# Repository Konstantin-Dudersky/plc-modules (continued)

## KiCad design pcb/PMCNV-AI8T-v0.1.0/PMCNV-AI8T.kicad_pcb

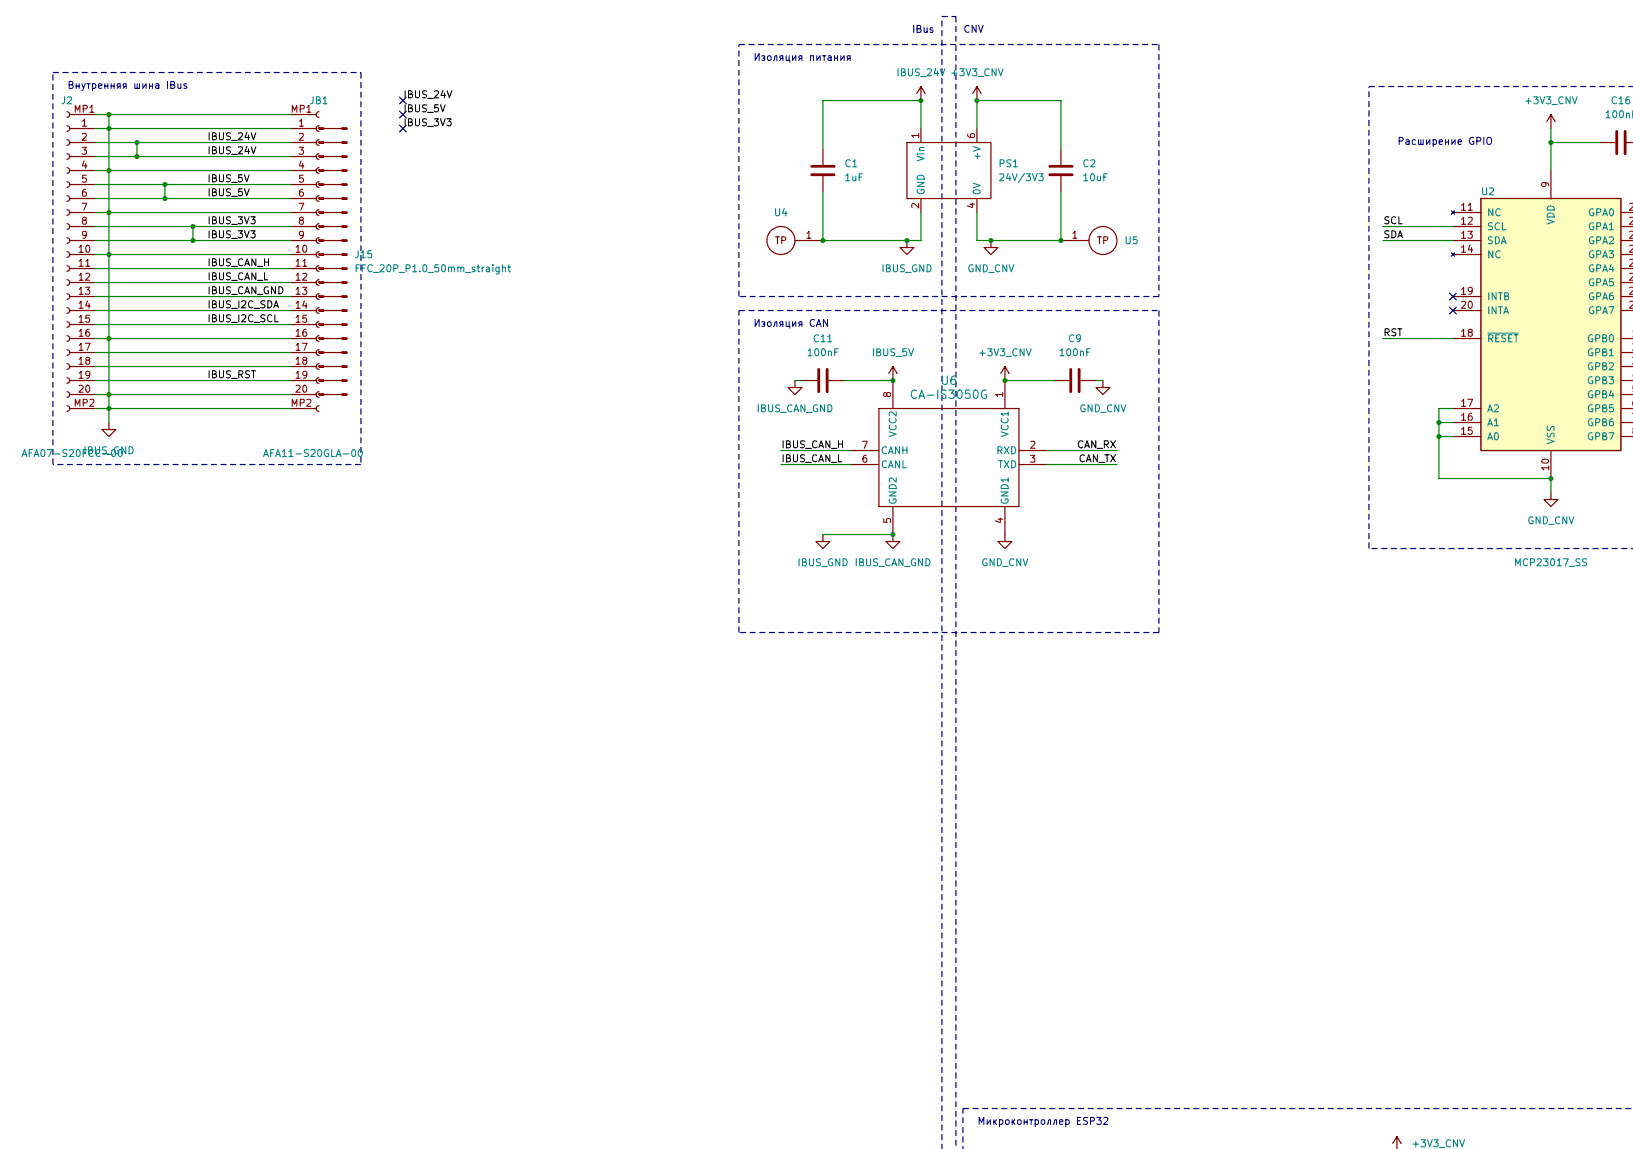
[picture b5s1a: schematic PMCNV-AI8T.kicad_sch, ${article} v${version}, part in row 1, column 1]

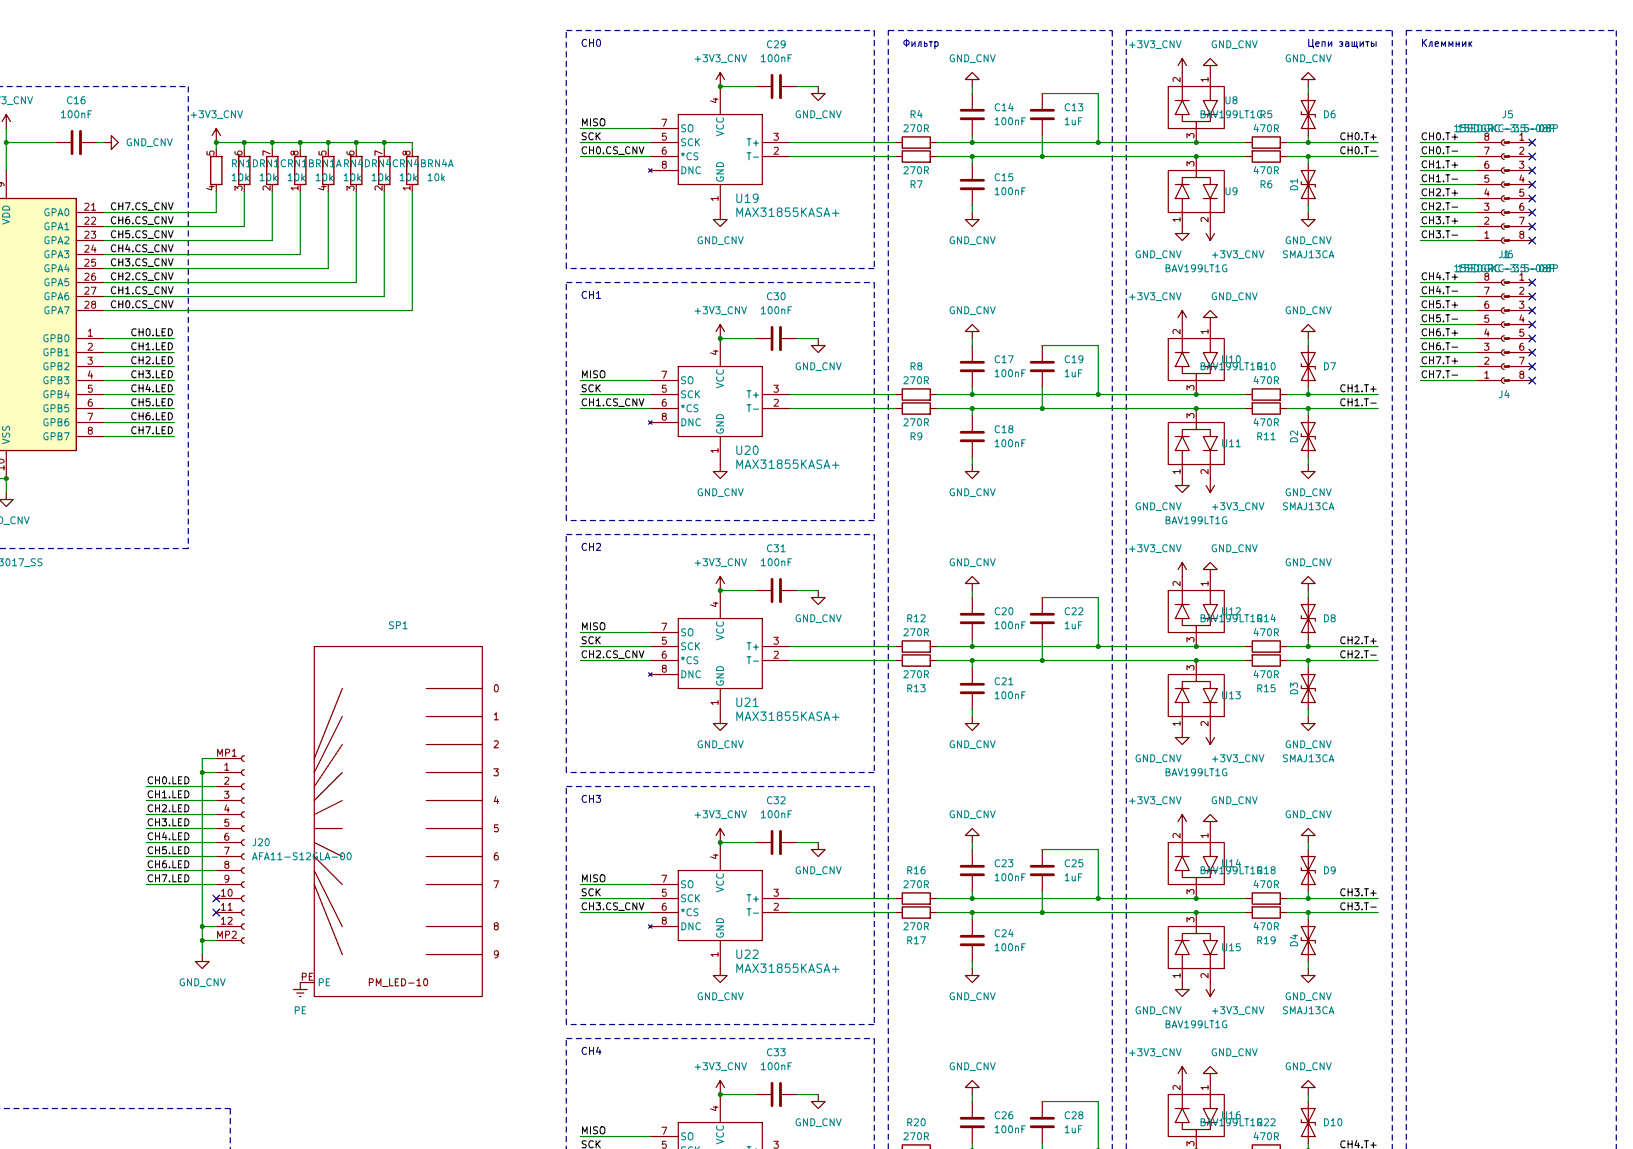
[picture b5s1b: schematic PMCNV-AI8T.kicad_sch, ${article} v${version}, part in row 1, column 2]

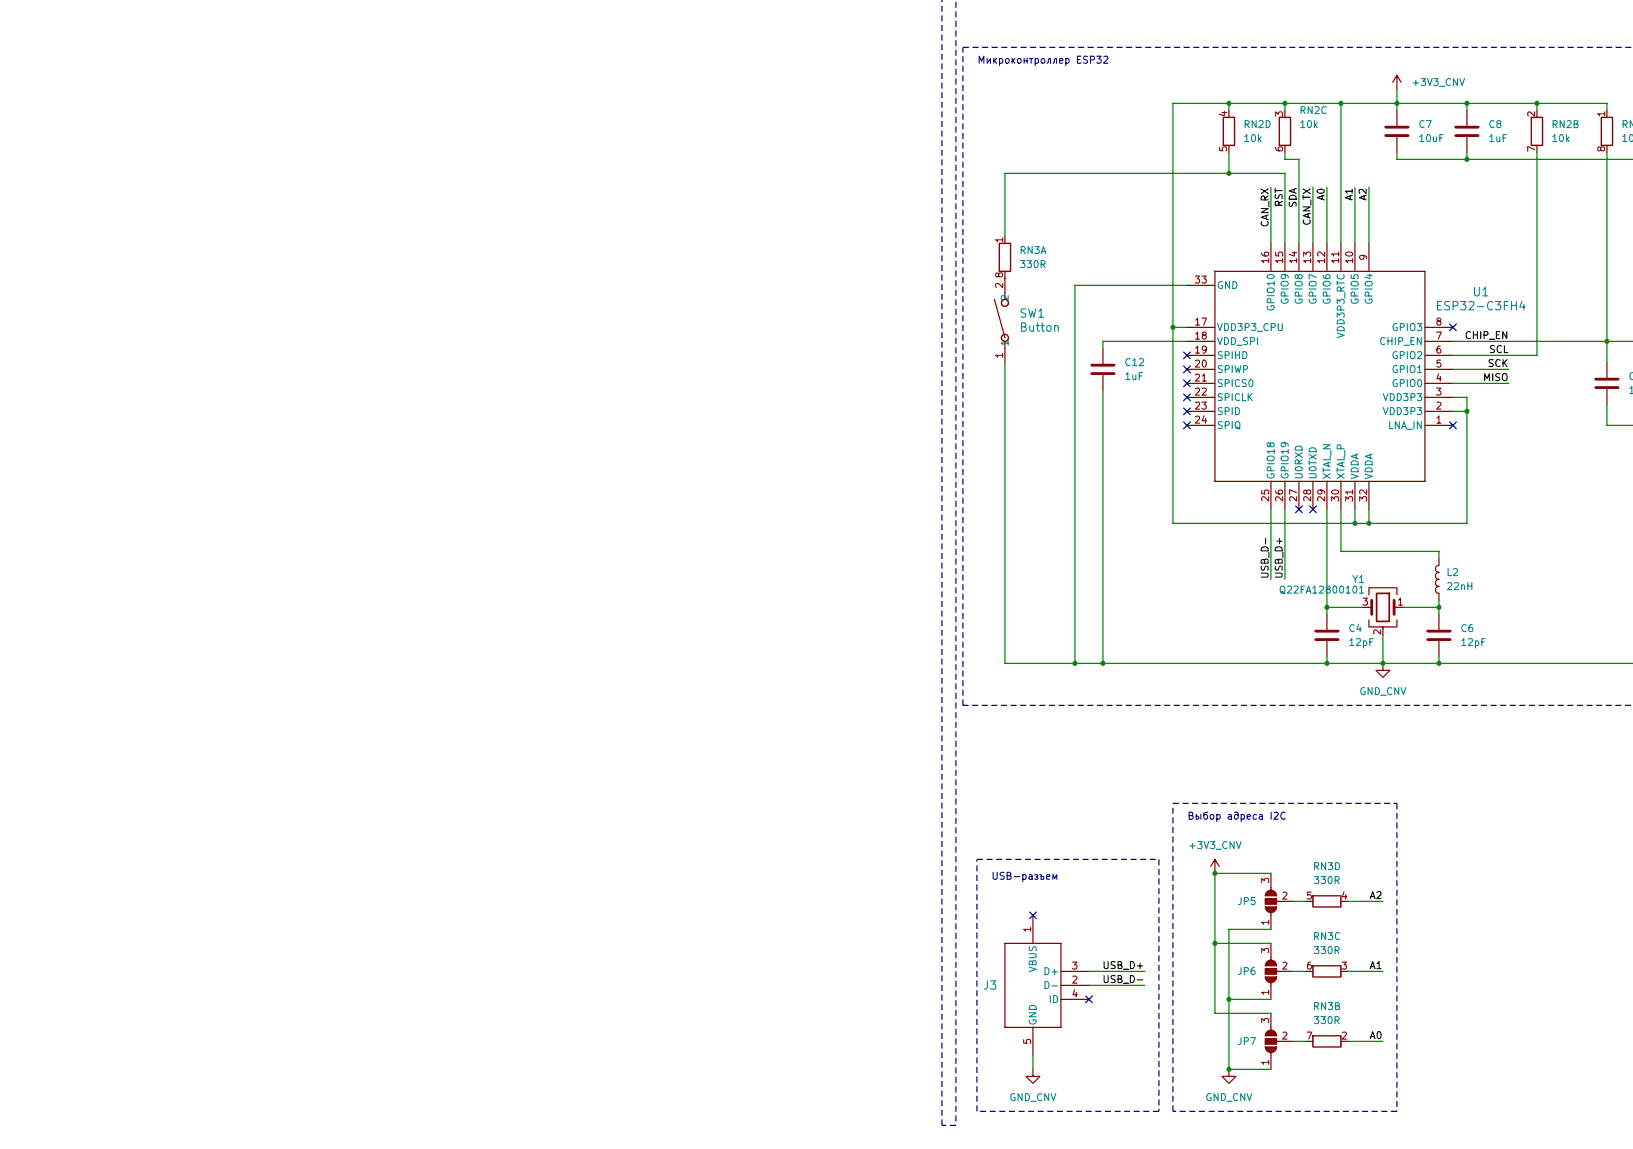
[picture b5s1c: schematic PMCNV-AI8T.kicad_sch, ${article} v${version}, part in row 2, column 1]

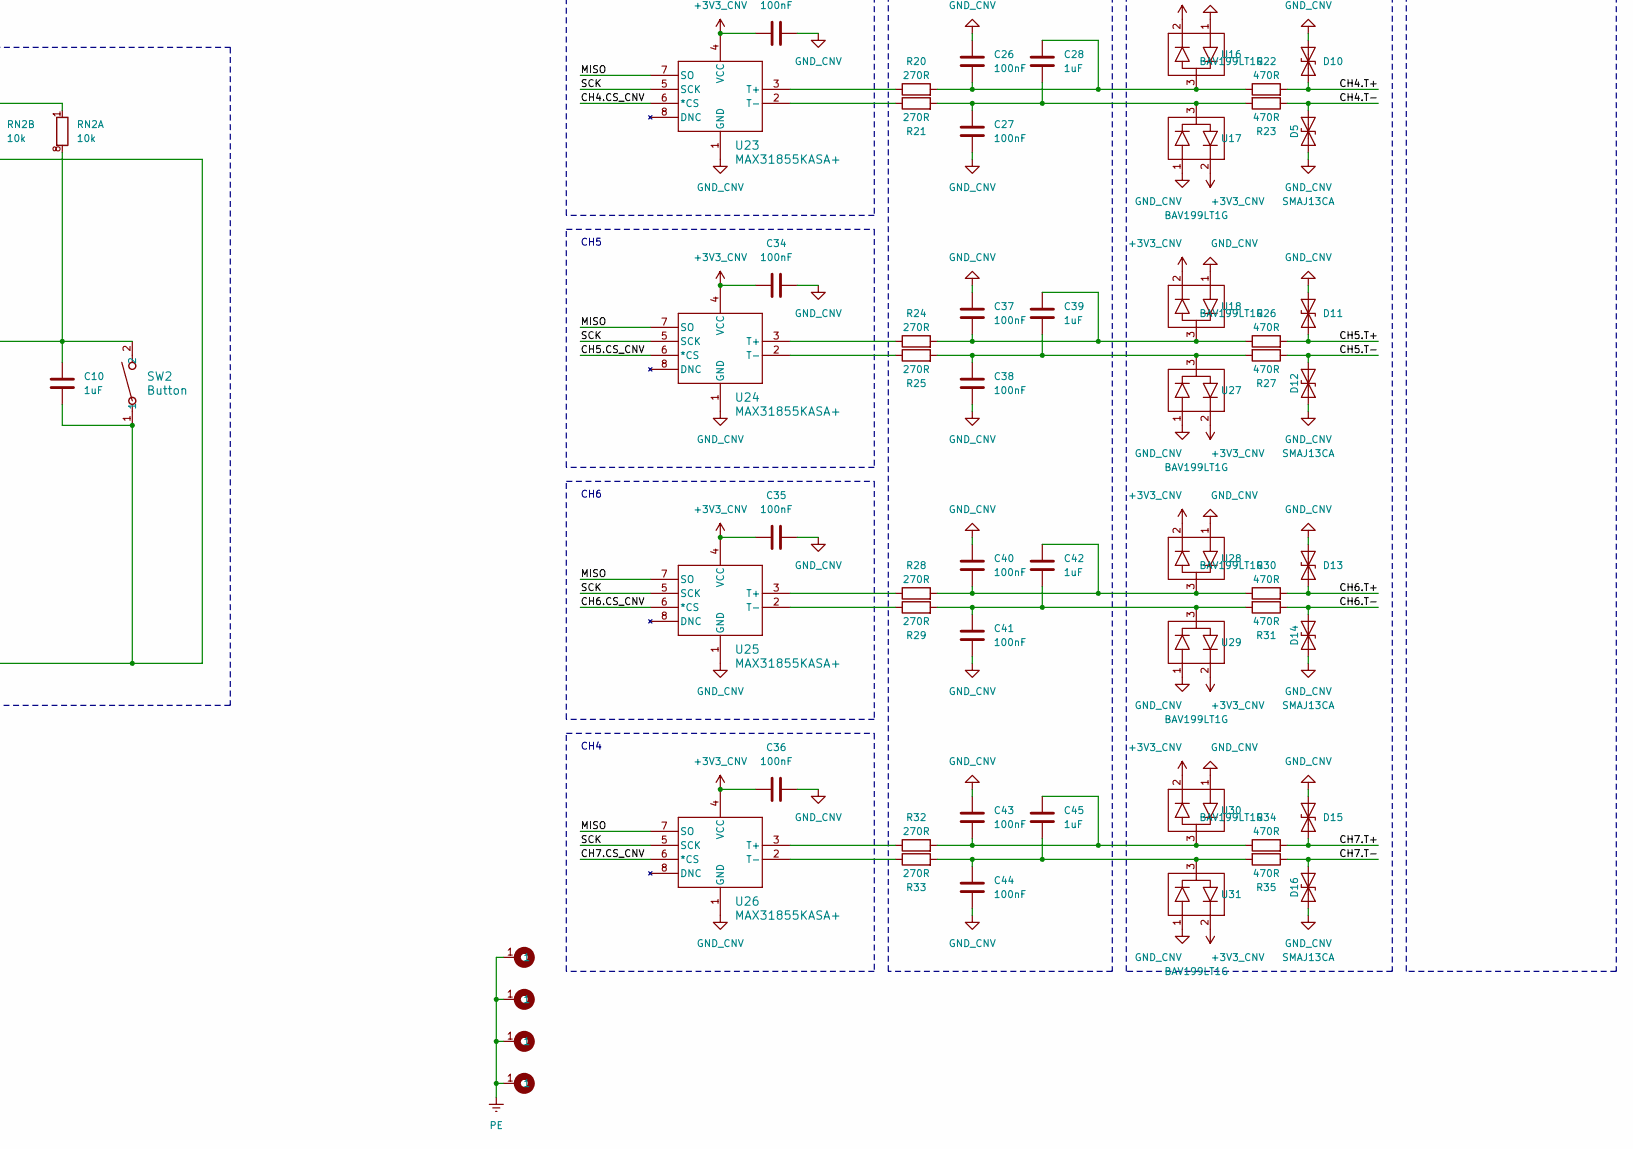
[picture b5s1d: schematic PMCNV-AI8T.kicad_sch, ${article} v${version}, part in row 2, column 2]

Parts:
C1, C8, C10, C12, C13, C19, C22, C25, C28, C39, C42, C45: 1uF; C_0603_1608Metric; part_ipn C_1uF_50V_0603_MLCC-X7R
C2, C7: 10uF; C_1206_3216Metric; part_ipn C_10uF_50V_1206_MLCC-X7R
C4, C6: 12pF; C_0603_1608Metric; part_ipn C_12pF_100V_0603_MLCC-NP0
C9, C11, C14, C15, C16, C17, C18, C20, C21, C23, C24, C26, C27, C29, C30, C31, C32, C33, C34, C35, C36, C37, C38, C40, C41, C43, C44: 100nF; C_0603_1608Metric; part_ipn C_100nF_100V_0603_MLCC-X7R
D1, D2, D3, D4, D5, D6, D7, D8, D9, D10, D11, D12, D13, D14, D15, D16: SMAJ13CA; SMASeries_LTF; part_ipn SMAJ13CA
H4, H5, H6, H7: M4; MountingHole_4.3mm_M4_Pad_Via
J1, J4: 15EDGRC-3.5-08P; part_ipn 15EDGRC-3.5-08P
J2: AFA07-S20FCC-00; AFA07S20FCA00; part_ipn AFA07-S20FCC-00
J3: U254-051T-4BH83-S1S; CONN5_H83-S1S_XKB; part_ipn U254-051T-4BH83-S1S
J5, J6: 15EDGKC-3.5-08P; part_ipn 15EDGKC-3.5-08P
J15: FFC_20P_P1.0_50mm_straight; part_ipn FFC_20P_P1.0_50mm_straight
J20: AFA11-S12GLA-00; part_ipn AFA11-S12GLA-00
JB1: AFA11-S20GLA-00; part_ipn AFA11-S20GLA-00
JP5, JP6, JP7: SolderJumper_3_Open; SolderJumper-3_P1.3mm_Open_Pad1.0x1.5mm
L2: 22nH; L_0603_1608Metric; part_ipn L_22nH_0603
PS1: 24V/3V3; B2405LS-1WR3; part_ipn B2403LS-1W
R4, R7, R8, R9, R12, R13, R16, R17, R20, R21, R24, R25, R28, R29, R32, R33: 270R; R_0603_1608Metric; part_ipn R_270R_0603_1%
R5, R6, R10, R11, R14, R15, R18, R19, R22, R23, R26, R27, R30, R31, R34, R35: 470R; R_0603_1608Metric; part_ipn R_470R_0603_1%
RN1, RN2, RN4: 10k; R_Array_Convex_4x0603; part_ipn R_10k_0603x4_1%
RN3: 330R; R_Array_Convex_4x0603; part_ipn R_330R_0603x4_1%
SP1: PMLED-xx-v0.0.3; part_ipn PMLED-10-v0.0.2
SW1, SW2: Button; SW_TS-1088_XNP-M; part_ipn TS-1088-AR02016
U1: ESP32-C3FH4; QFN32_5X5_EXP; part_ipn ESP32-C3FH4
U2: MCP23017_SS; SSOP28_MC_MCH; part_ipn MCP23017-E/SS
U4, U5: 5117; part_ipn Keystone_5117
U6: CA-IS3050G; SOIC8_CA-IS305_CLG; part_ipn CA-IS3050G
U8, U9, U10, U11, U12, U13, U14, U15, U16, U17, U18, U27, U28, U29, U30, U31: BAV199LT1G; SOT-23_ONS; part_ipn BAV199LT1G
U19, U20, U21, U22, U23, U24, U25, U26: MAX31855KASA+; 21-0041B_8_MXM; part_ipn MAX31855KASA+
Y1: Q22FA12800101; Crystal_SMD_2016-4Pin_2.0x1.6mm; part_ipn Q22FA12800101

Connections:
+3V3_CNV: C2.1, C7.1, C8.1, C9.1, C16.1, C29.1, C30.1, C31.1, C32.1, C33.1, C34.1, C35.1, C36.1, JP5.3 (B), JP6.3 (B), JP7.3 (B), PS1.6 (+V), RN1.5 (R4.2), RN1.6 (R3.2), RN1.7 (R2.2), RN1.8 (R1.2), RN2.1 (R1.1), RN2.2 (R2.1), RN2.3 (R3.1), RN2.4 (R4.1), RN4.5 (R4.2), RN4.6 (R3.2), RN4.7 (R2.2), RN4.8 (R1.2), U1.2 (VDD3P3), U1.3 (VDD3P3), U1.11 (VDD3P3_RTC), U1.17 (VDD3P3_CPU), U1.31 (VDDA), U1.32 (VDDA), U2.9 (VDD), U6.1 (VCC1), U8.2, U9.2, U10.2, U11.2, U12.2, U13.2, U14.2, U15.2, U16.2, U17.2, U18.2, U19.4 (VCC), U20.4 (VCC), U21.4 (VCC), U22.4 (VCC), U23.4 (VCC), U24.4 (VCC), U25.4 (VCC), U26.4 (VCC), U27.2, U28.2, U29.2, U30.2, U31.2
/A0: RN3.2 (R2.1), U1.12 (GPIO6)
/A1: RN3.3 (R3.1), U1.10 (GPIO5)
/A2: RN3.4 (R4.1), U1.9 (GPIO4)
/CAN_RX: U1.16 (GPIO10), U6.2 (RXD)
/CAN_TX: U1.13 (GPIO7), U6.3 (TXD)
/CH0.CS_CNV: RN4.1 (R1.1), U2.28 (GPA7), U19.6 (*CS)
/CH0.LED: J20.2, U2.1 (GPB0)
/CH0.T+: D6.2 (A2), J1.8, R5.2
/CH0.T-: D1.2 (A2), J1.7, R6.1
/CH1.CS_CNV: RN4.2 (R2.1), U2.27 (GPA6), U20.6 (*CS)
/CH1.LED: J20.3, U2.2 (GPB1)
/CH1.T+: D7.2 (A2), J1.6, R10.2
/CH1.T-: D2.2 (A2), J1.5, R11.1
/CH2.CS_CNV: RN4.3 (R3.1), U2.26 (GPA5), U21.6 (*CS)
/CH2.LED: J20.4, U2.3 (GPB2)
/CH2.T+: D8.2 (A2), J1.4, R14.2
/CH2.T-: D3.2 (A2), J1.3, R15.1
/CH3.CS_CNV: RN4.4 (R4.1), U2.25 (GPA4), U22.6 (*CS)
/CH3.LED: J20.5, U2.4 (GPB3)
/CH3.T+: D9.2 (A2), J1.2, R18.2
/CH3.T-: D4.2 (A2), J1.1, R19.1
/CH4.CS_CNV: RN1.1 (R1.1), U2.24 (GPA3), U23.6 (*CS)
/CH4.LED: J20.6, U2.5 (GPB4)
/CH4.T+: D10.2 (A2), J4.8, R22.2
/CH4.T-: D5.2 (A2), J4.7, R23.1
/CH5.CS_CNV: RN1.2 (R2.1), U2.23 (GPA2), U24.6 (*CS)
/CH5.LED: J20.7, U2.6 (GPB5)
/CH5.T+: D11.2 (A2), J4.6, R26.2
/CH5.T-: D12.2 (A2), J4.5, R27.1
/CH6.CS_CNV: RN1.3 (R3.1), U2.22 (GPA1), U25.6 (*CS)
/CH6.LED: J20.8, U2.7 (GPB6)
/CH6.T+: D13.2 (A2), J4.4, R30.2
/CH6.T-: D14.2 (A2), J4.3, R31.1
/CH7.CS_CNV: RN1.4 (R4.1), U2.21 (GPA0), U26.6 (*CS)
/CH7.LED: J20.9, U2.8 (GPB7)
/CH7.T+: D15.2 (A2), J4.2, R34.2
/CH7.T-: D16.2 (A2), J4.1, R35.1
/CHIP_EN: C10.1, RN2.8 (R1.2), SW2.2, U1.7 (CHIP_EN)
/IBUS_3V3: J2.8, J2.9, JB1.8, JB1.9
/IBUS_CAN_H: J2.11, JB1.11, U6.7 (CANH)
/IBUS_CAN_L: J2.12 (Pin_11), JB1.12 (Pin_11), U6.6 (CANL)
/IBUS_I2C_SCL: J2.15 (Pin_11), JB1.15 (Pin_11)
/IBUS_I2C_SDA: J2.14 (Pin_11), JB1.14 (Pin_11)
/IBUS_RST: J2.19 (Pin_11), JB1.19 (Pin_11)
/MISO: U1.4 (GPIO0), U19.7 (SO), U20.7 (SO), U21.7 (SO), U22.7 (SO), U23.7 (SO), U24.7 (SO), U25.7 (SO), U26.7 (SO)
/RST: RN2.5 (R4.2), RN3.1 (R1.1), U1.15 (GPIO9), U2.18 (~RESET)
/SCK: U1.5 (GPIO1), U19.5 (SCK), U20.5 (SCK), U21.5 (SCK), U22.5 (SCK), U23.5 (SCK), U24.5 (SCK), U25.5 (SCK), U26.5 (SCK)
/SCL: RN2.7 (R2.2), U1.6 (GPIO2), U2.12 (SCL)
/SDA: RN2.6 (R3.2), U1.14 (GPIO8), U2.13 (SDA)
/USB_D+: J3.3 (D+), U1.26 (GPIO19)
/USB_D-: J3.2 (D-), U1.25 (GPIO18)
GND_CNV: C2.2, C4.2, C6.2, C7.2, C8.2, C9.2, C10.2, C12.2, C14.1, C15.2, C16.2, C17.1, C18.2, C20.1, C21.2, C23.1, C24.2, C26.1, C27.2, C29.2, C30.2, C31.2, C32.2, C33.2, C34.2, C35.2, C36.2, C37.1, C38.2, C40.1, C41.2, C43.1, C44.2, D1.1 (A1), D2.1 (A1), D3.1 (A1), D4.1 (A1), D5.1 (A1), D6.1 (A1), D7.1 (A1), D8.1 (A1), D9.1 (A1), D10.1 (A1), D11.1 (A1), D12.1 (A1), D13.1 (A1), D14.1 (A1), D15.1 (A1), D16.1 (A1), J3.5 (GND), J20.1, J20.12 (Pin_11), J20.MP1 (Pin_11), J20.MP2 (Pin_11), JP5.1 (A), JP6.1 (A), JP7.1 (A), PS1.4 (0V), SW1.1, SW2.1, U1.33 (GND), U2.10 (VSS), U2.15 (A0), U2.16 (A1), U2.17 (A2), U5.1, U6.4 (GND1), U8.1, U9.1, U10.1, U11.1, U12.1, U13.1, U14.1, U15.1, U16.1, U17.1, U18.1, U19.1 (GND), U20.1 (GND), U21.1 (GND), U22.1 (GND), U23.1 (GND), U24.1 (GND), U25.1 (GND), U26.1 (GND), U27.1, U28.1, U29.1, U30.1, U31.1, Y1.2 (G), Y1.4 (G)
IBUS_5V: C11.2, J2.5, J2.6, JB1.5, JB1.6, U6.8 (VCC2)
IBUS_24V: C1.1, J2.2, J2.3, JB1.2, JB1.3, PS1.1 (Vin)
IBUS_CAN_GND: C1.2, C11.1, J2.1, J2.4, J2.7, J2.10, J2.13 (Pin_11), J2.16 (Pin_11), J2.20 (Pin_11), J2.MP1 (Pin_11), J2.MP2 (Pin_11), JB1.1, JB1.4, JB1.7, JB1.10, JB1.13 (Pin_11), JB1.16 (Pin_11), JB1.20 (Pin_11), JB1.MP1 (Pin_11), JB1.MP2 (Pin_11), PS1.2 (GND), U4.1, U6.5 (GND2)
unnamed: C6.1, L2.1, Y1.1
unnamed: C13.1, C14.2, R4.2, R5.1, U8.3
unnamed: C13.2, C15.1, R6.2, R7.2, U9.3
unnamed: C17.2, C19.1, R8.2, R10.1, U10.3
unnamed: C18.1, C19.2, R9.2, R11.2, U11.3
unnamed: C20.2, C22.1, R12.2, R14.1, U12.3
unnamed: C21.1, C22.2, R13.2, R15.2, U13.3
unnamed: C23.2, C25.1, R16.2, R18.1, U14.3
unnamed: C24.1, C25.2, R17.2, R19.2, U15.3
unnamed: C26.2, C28.1, R20.2, R22.1, U16.3
unnamed: C27.1, C28.2, R21.2, R23.2, U17.3
unnamed: C37.2, C39.1, R24.2, R26.1, U18.3
unnamed: C38.1, C39.2, R25.2, R27.2, U27.3
unnamed: C40.2, C42.1, R28.2, R30.1, U28.3
unnamed: C41.1, C42.2, R29.2, R31.2, U29.3
unnamed: C43.2, C45.1, R32.2, R34.1, U30.3
unnamed: C44.1, C45.2, R33.2, R35.2, U31.3
unnamed: J2.17 (Pin_11), JB1.17 (Pin_11)
unnamed: J2.18 (Pin_11), JB1.18 (Pin_11)
unnamed: JP5.2 (C), RN3.5 (R4.2)
unnamed: JP6.2 (C), RN3.6 (R3.2)
unnamed: JP7.2 (C), RN3.7 (R2.2)
unnamed: RN3.8 (R1.2), SW1.2
unnamed: C12.1, U1.18 (VDD_SPI)
unnamed: C4.1, U1.29 (XTAL_N), Y1.3
unnamed: L2.2, U1.30 (XTAL_P)
unnamed: R4.1, U19.3 (T+)
unnamed: R7.1, U19.2 (T-)
unnamed: R8.1, U20.3 (T+)
unnamed: R9.1, U20.2 (T-)
unnamed: R12.1, U21.3 (T+)
unnamed: R13.1, U21.2 (T-)
unnamed: R16.1, U22.3 (T+)
unnamed: R17.1, U22.2 (T-)
unnamed: R20.1, U23.3 (T+)
unnamed: R21.1, U23.2 (T-)
unnamed: R24.1, U24.3 (T+)
unnamed: R25.1, U24.2 (T-)
unnamed: R28.1, U25.3 (T+)
unnamed: R29.1, U25.2 (T-)
unnamed: R32.1, U26.3 (T+)
unnamed: R33.1, U26.2 (T-)
PE: H4.1 (1_1), H5.1 (1_1), H6.1 (1_1), H7.1 (1_1), SP1.PE (PE_PE)

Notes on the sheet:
CH4
IBus
Изоляция питания
Выбор адреса I2C
CH3
CH1
Внутренняя шина IBus
CH2
CH6
CH0
CH5
USB-разъем
Расширение GPIO
CNV
Микроконтроллер ESP32
Изоляция CAN
Фильтр
Цепи защиты
Клеммник

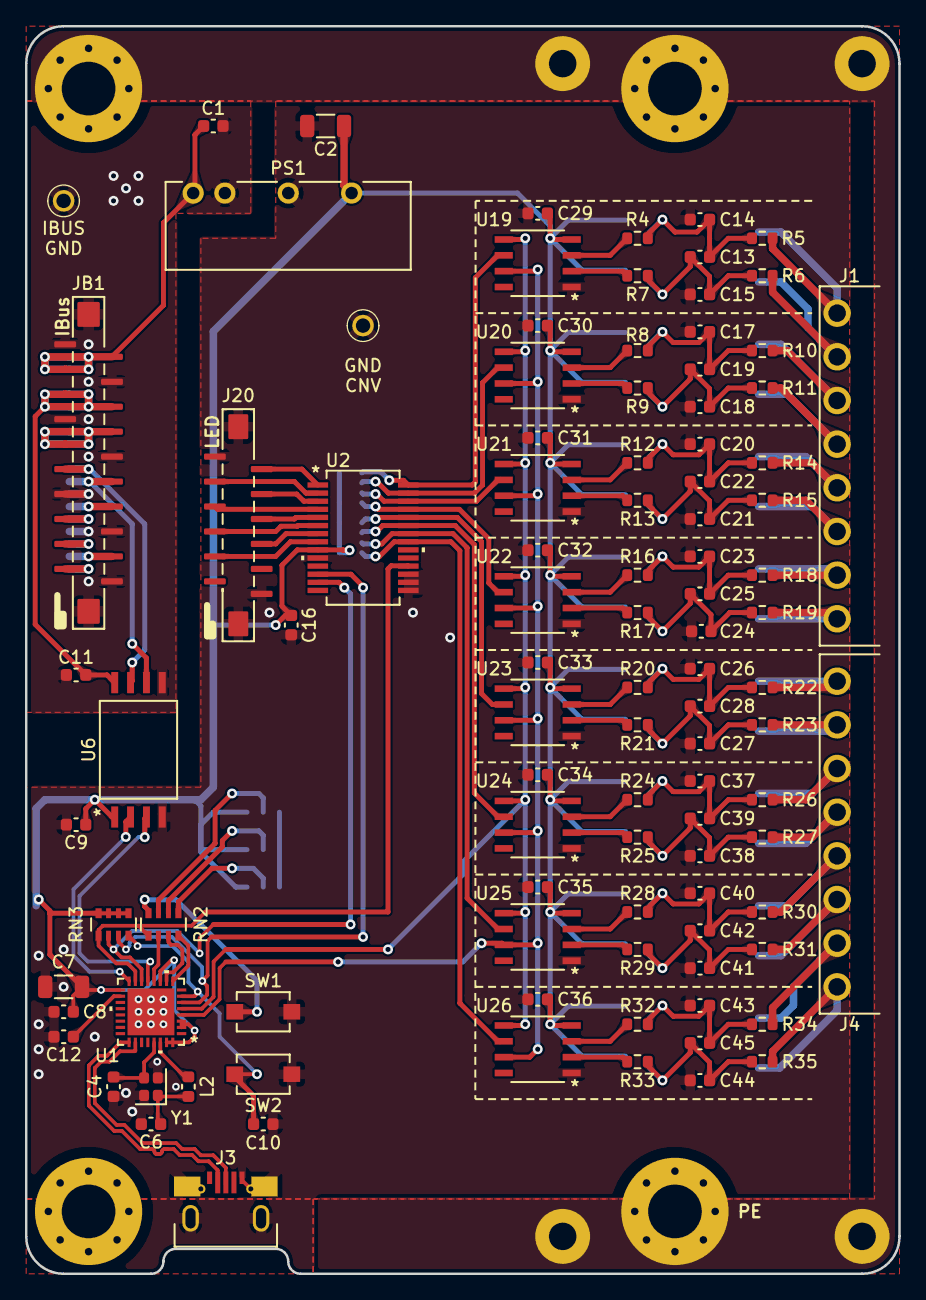
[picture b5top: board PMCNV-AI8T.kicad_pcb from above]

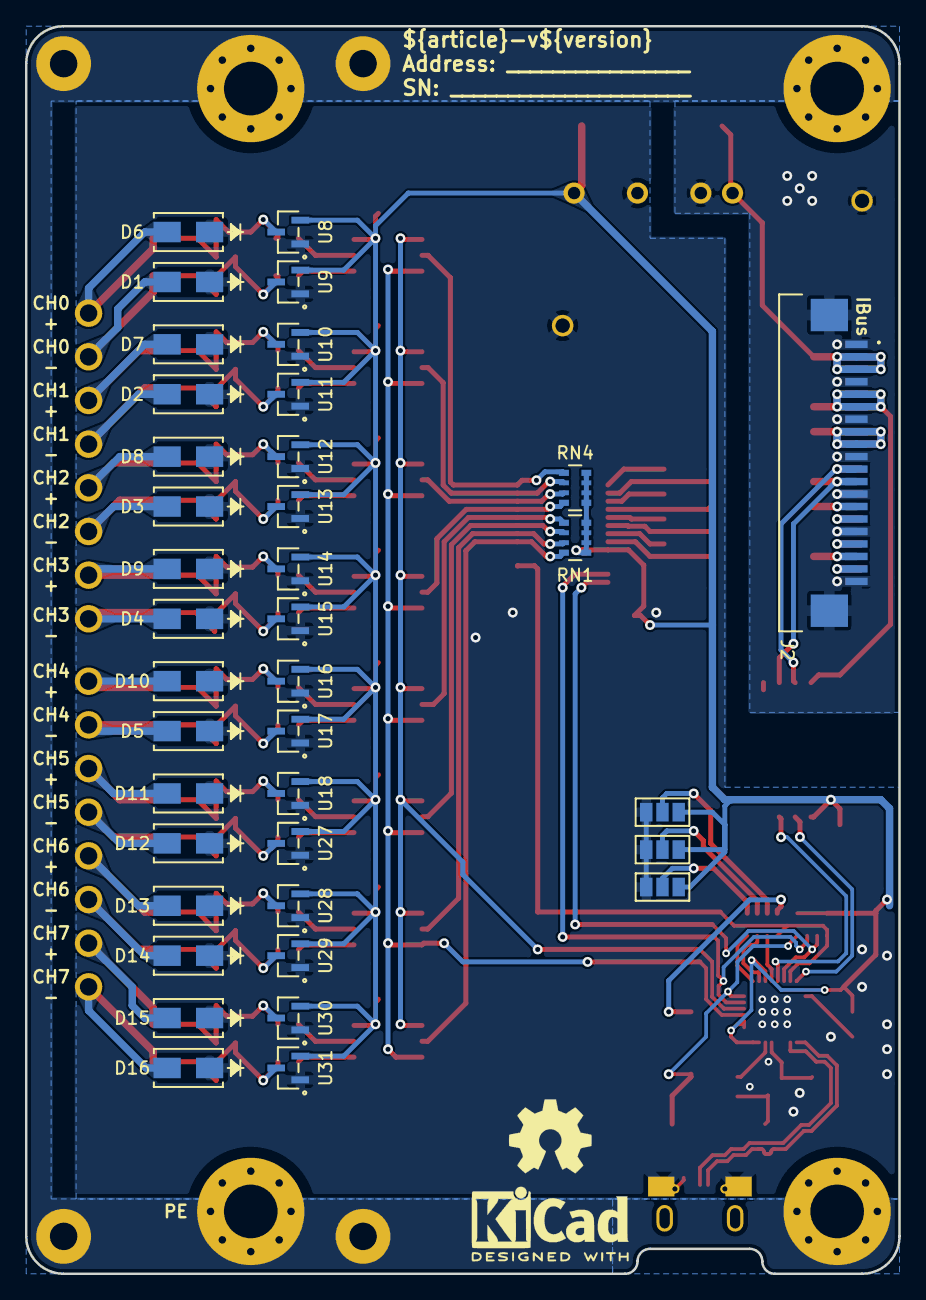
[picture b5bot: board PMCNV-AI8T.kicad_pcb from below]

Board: 2 copper layers, 70.0 x 100.0 mm, 145 parts (40 on the bottom side), 99 nets.

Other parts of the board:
kicad_logo: KiCad-Logo2_5mm_SilkScreen
oshw_logo: OSHW-Symbol_6.7x6mm_SilkScreen

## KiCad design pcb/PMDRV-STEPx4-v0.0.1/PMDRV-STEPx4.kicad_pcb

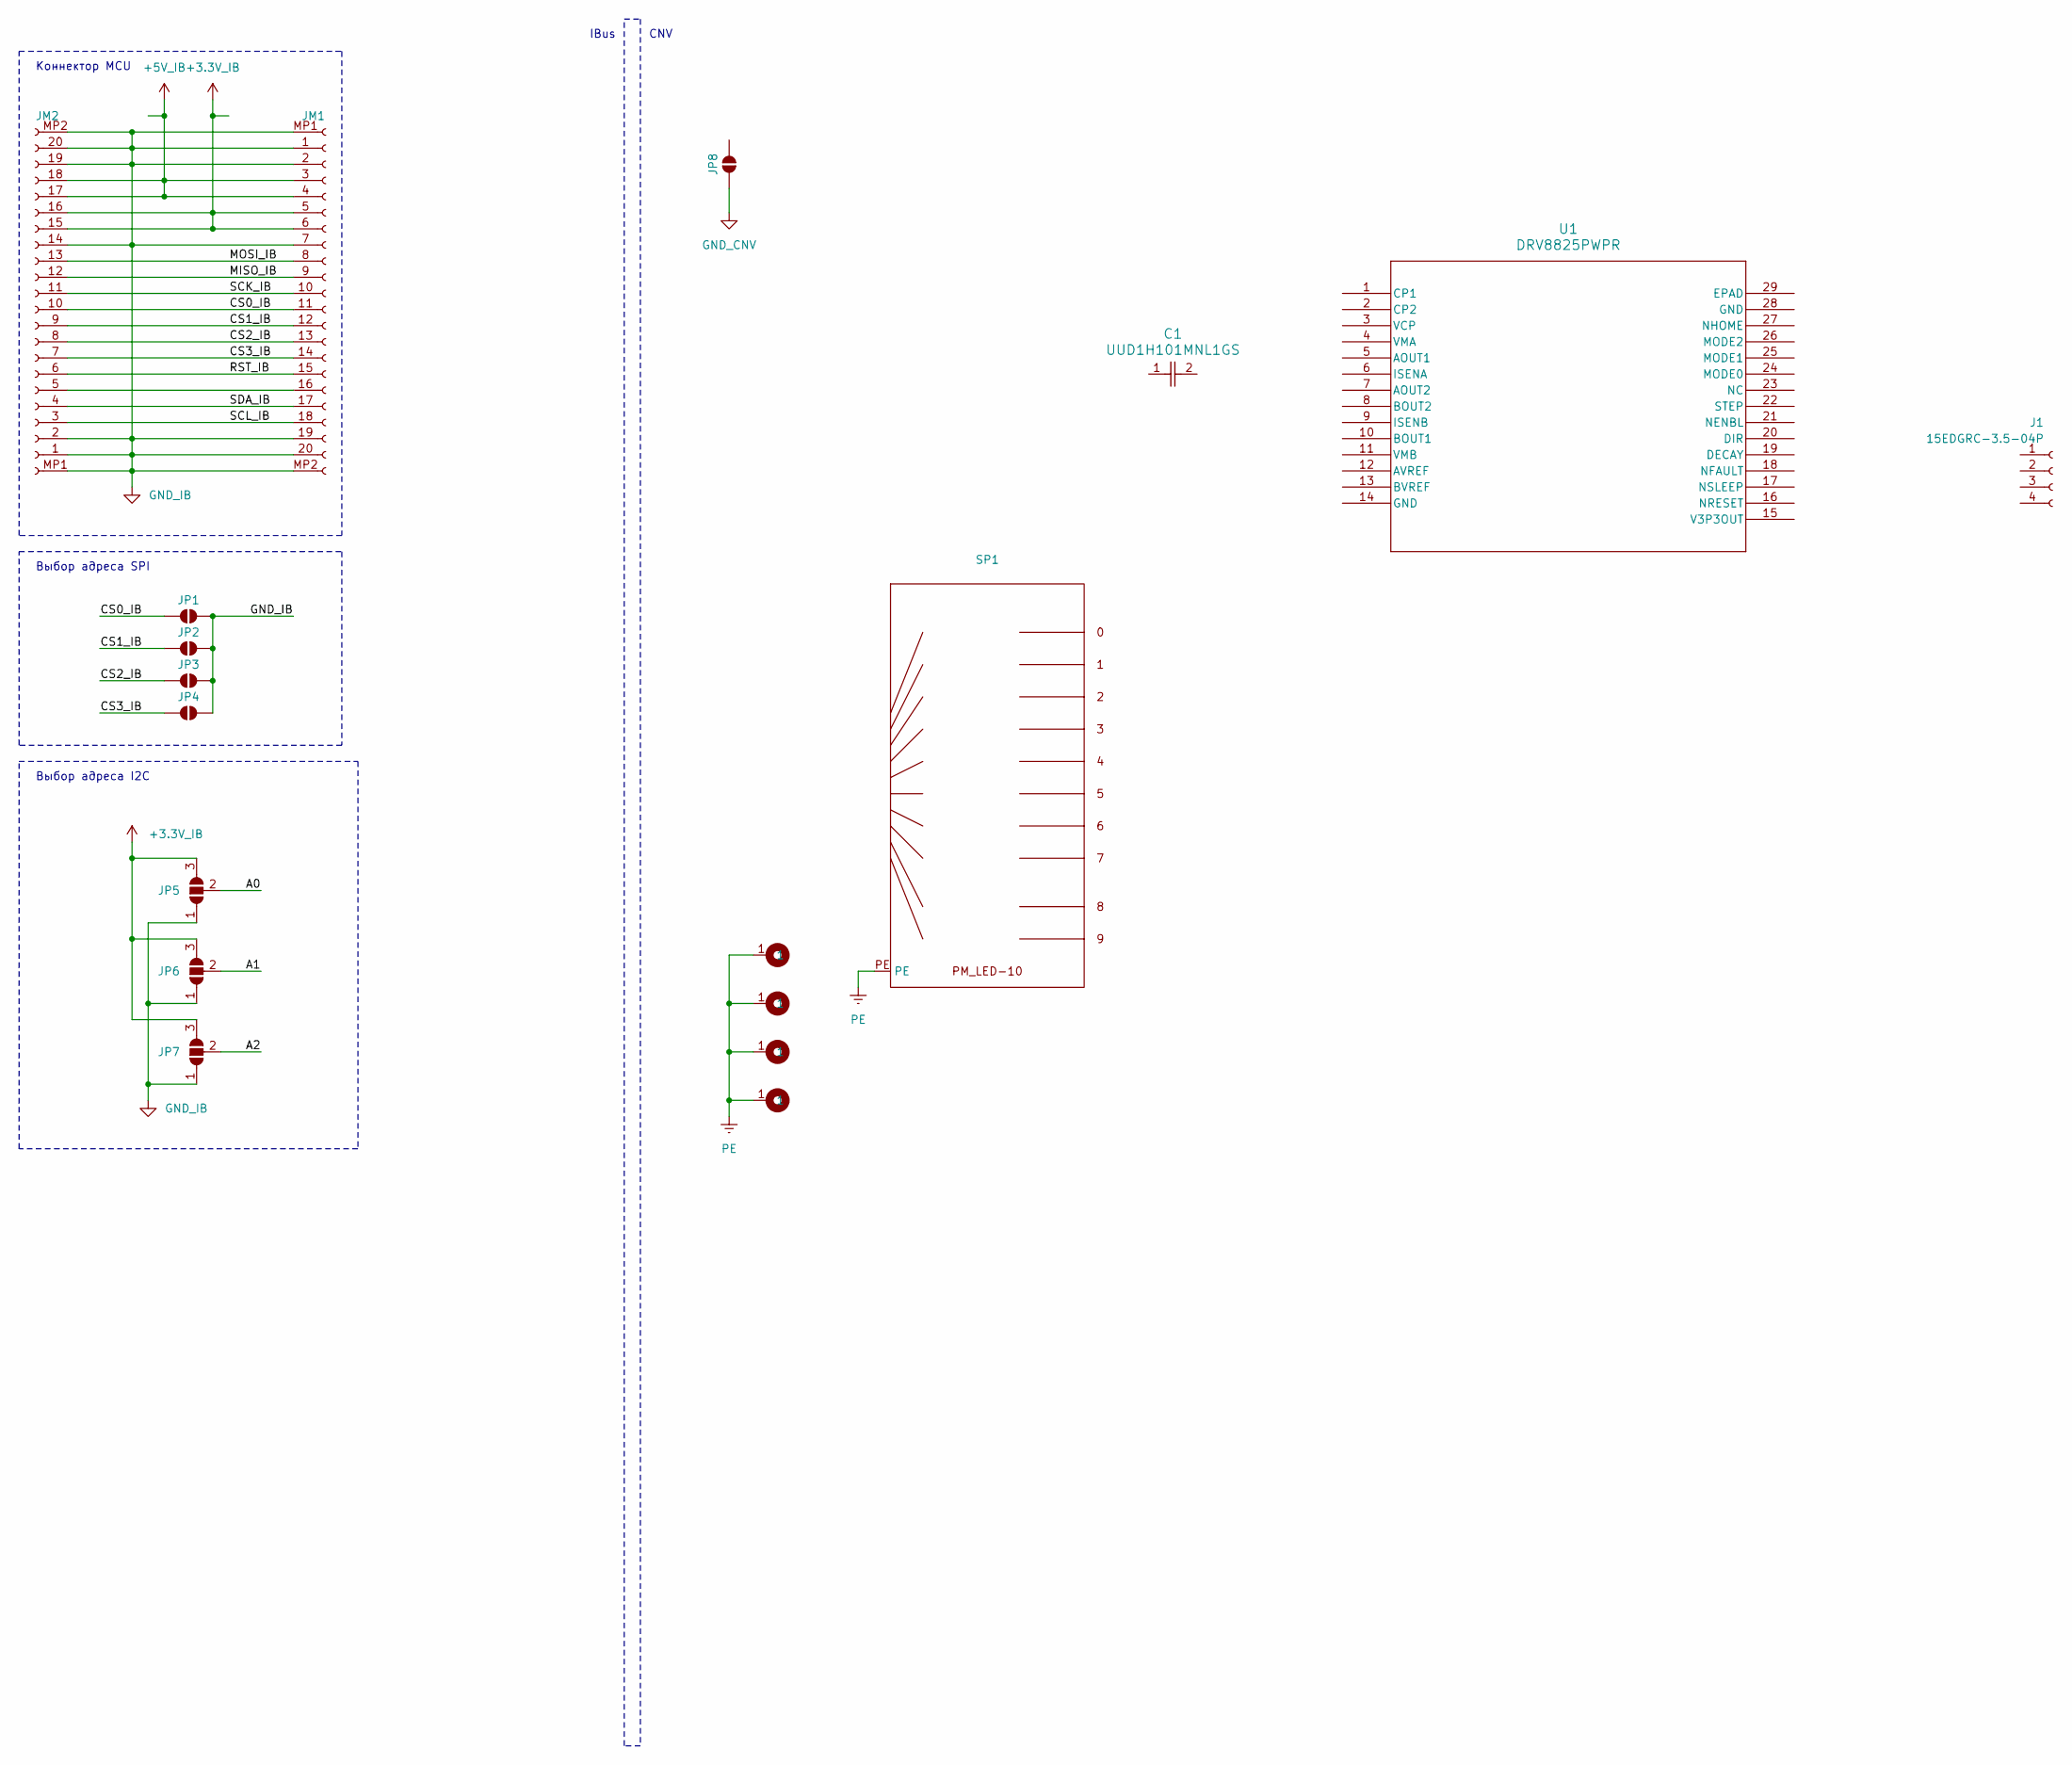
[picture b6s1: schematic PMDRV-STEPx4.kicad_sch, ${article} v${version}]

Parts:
C1: UUD1H101MNL1GS; U2-P_NCH
H1, H2, H3, H4: M4; MountingHole_4.3mm_M4_Pad_Via
J1: 15EDGRC-3.5-04P; part_ipn 15EDGRC-3.5-04P
JM1, JM2: AFA07-S20FCC-00; AFA11-S20GLA-00; part_ipn AFA11-S20GLA-00
JP1, JP2, JP3, JP4, JP8: SolderJumper_2_Open; SolderJumper-2_P1.3mm_Open_Pad1.0x1.5mm
JP5, JP6, JP7: SolderJumper_3_Open; SolderJumper-3_P1.3mm_Open_Pad1.0x1.5mm
SP1: PMLED-xx-v0.0.3; part_ipn PMLED-10-v0.0.2
U1: DRV8825PWPR; PWP28_5P18X3P1

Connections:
+3.3V_IB: JM1.5, JM1.6, JM2.15 (Pin_11), JM2.16 (Pin_11), JP5.3 (B), JP6.3 (B), JP7.3 (B)
+5V_IB: JM1.3, JM1.4, JM2.17 (Pin_11), JM2.18 (Pin_11)
/A0: JP5.2 (C)
/A1: JP6.2 (C)
/A2: JP7.2 (C)
/CS0_IB: JM1.11, JM2.10, JP1.1 (A)
/CS1_IB: JM1.12 (Pin_11), JM2.9, JP2.1 (A)
/CS2_IB: JM1.13 (Pin_11), JM2.8, JP3.1 (A)
/CS3_IB: JM1.14 (Pin_11), JM2.7, JP4.1 (A)
/MISO_IB: JM1.9, JM2.12 (Pin_11)
/MOSI_IB: JM1.8, JM2.13 (Pin_11)
/RST_IB: JM1.15 (Pin_11), JM2.6
/SCK_IB: JM1.10, JM2.11
/SCL_IB: JM1.18 (Pin_11), JM2.3
/SDA_IB: JM1.17 (Pin_11), JM2.4
GND_CNV: JP8.1 (A_1)
GND_IB: JM1.1, JM1.2, JM1.7, JM1.19 (Pin_11), JM1.20 (Pin_11), JM1.MP1 (Pin_11), JM1.MP2 (Pin_11), JM2.1, JM2.2, JM2.14 (Pin_11), JM2.19 (Pin_11), JM2.20 (Pin_11), JM2.MP1 (Pin_11), JM2.MP2 (Pin_11), JP1.2 (B), JP2.2 (B), JP3.2 (B), JP4.2 (B), JP5.1 (A), JP6.1 (A), JP7.1 (A)
unnamed: JM1.16 (Pin_11), JM2.5
PE: H1.1 (1_1), H2.1 (1_1), H3.1 (1_1), H4.1 (1_1), SP1.PE (PE_PE)

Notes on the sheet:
IBus
Выбор адреса I2C
CNV
Выбор адреса SPI
Коннектор MCU
